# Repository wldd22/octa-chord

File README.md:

# Octa Chord

A 12-key MIDI keyboard with rotary encoders, key switches, and capacitive touch pads.

## Details
PCB made in **KiCad**<br>
Firmware in **KMK**

**Components**:
- **Waveshare ESP32-S3-Zero**: Microcontroller
- **MPR121 Breakout V12**: Capacitive Touch Sensor Control Module
- **Kailh Choc v1 Switches**: Key switches
- **Chocfox CFX Choc Blank Keycaps**: Keycaps
- **Hongyan EC11H 7CE20P1ZD20**: Rotary encoders

**Features**:
- **12 capacitive touch pad keys**, one octave on a piano
- **6 key switches** in a **3x2 grid**, each with an **LED**
- **2 rotary encoders** with switches
- **ESP32 microcontroller** with a **USB-C port** and **15 GPIO pins**

## About
Before making this project, I barely knew anything about MIDI, but I was curious to learn how it
worked and use it to make simple music. So, for week 2 (Music week) of Hack Club's Half Life, I
was excited to make a simple MIDI controller I could use and learn from.

My original plan was far more ambitious than the final version. See [JOURNAL.md](JOURNAL.md) for some
of the many iterations I went through of the layout and overall design. I had to make many compromises
and changes so the final product was useful, feasible, and something I could be happy with.

## Images

### Schematic

### PCB Routing

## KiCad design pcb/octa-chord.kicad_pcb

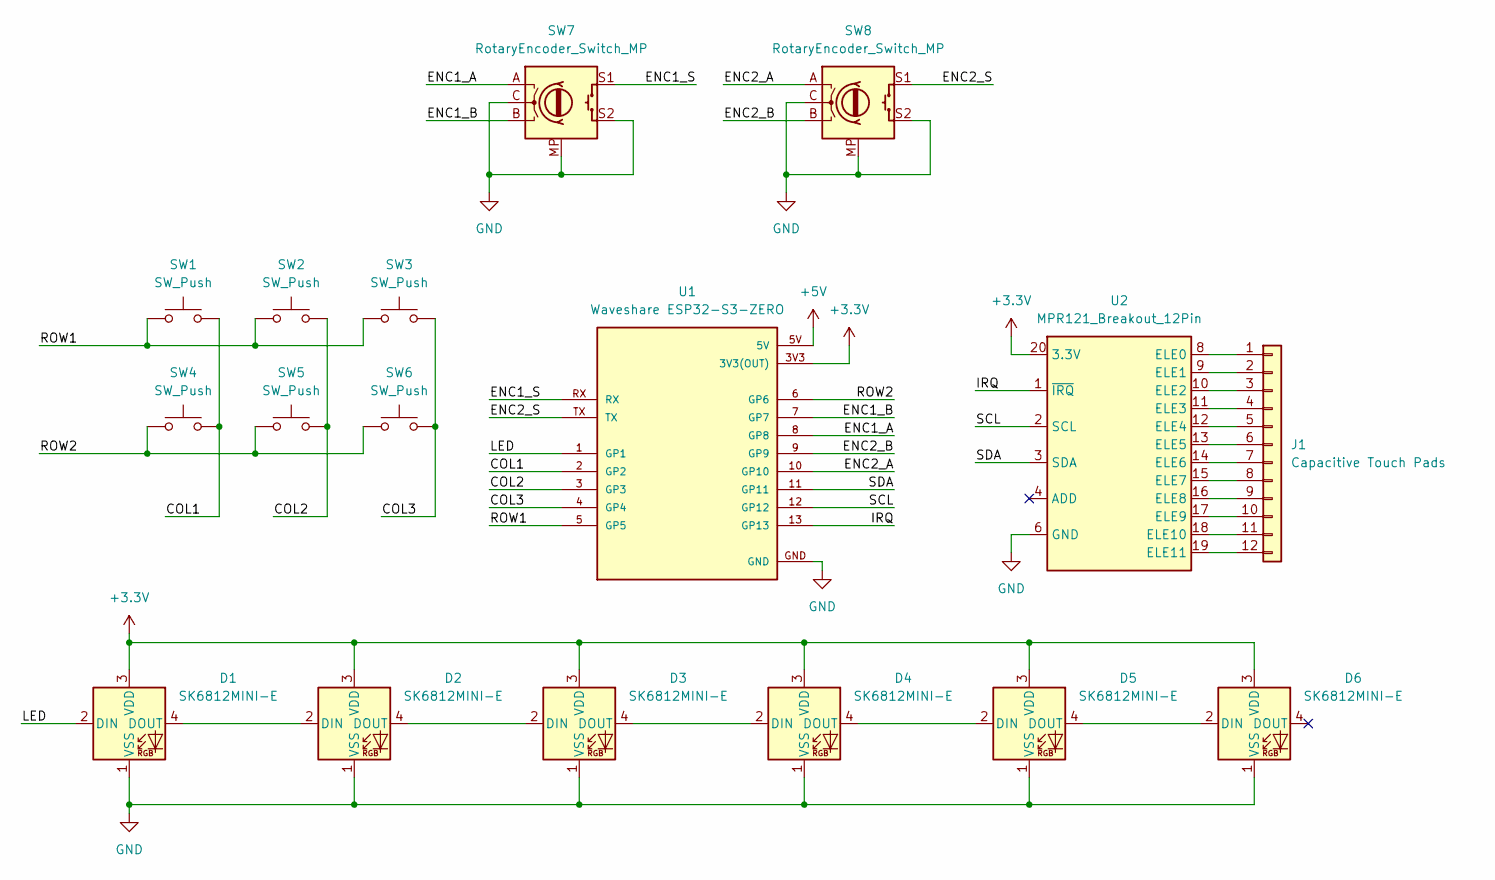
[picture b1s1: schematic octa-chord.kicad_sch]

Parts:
D1, D2, D3, D4, D5, D6: SK6812MINI-E; LED_SK6812MINI-E_3.2x2.8mm_P1.5mm_ReverseMount
J1: Capacitive Touch Pads; Capactive Key Octave
SW1, SW2, SW3, SW4, SW5, SW6: SW_Push; Kailh Choc Low-Profile Switches
SW7, SW8: RotaryEncoder_Switch_MP; RotaryEncoder_Alps_EC11E-Switch_Vertical_H20mm
U1: Waveshare ESP32-S3-ZERO; Waveshare ESP32-S3-Zero; PARTREV NA
U2: MPR121_Breakout_12Pin

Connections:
+3.3V: D1.3 (VDD), D2.3 (VDD), D3.3 (VDD), D4.3 (VDD), D5.3 (VDD), D6.3 (VDD), U1.3V3 (3V3(OUT)), U2.20 (3.3V)
+5V: U1.5V
/COL1: SW1.2, SW4.2, U1.2 (GP2)
/COL2: SW2.2, SW5.2, U1.3 (GP3)
/COL3: SW3.2, SW6.2, U1.4 (GP4)
/ENC1_A: SW7.A, U1.8 (GP8)
/ENC1_B: SW7.B, U1.7 (GP7)
/ENC1_S: SW7.S1, U1.RX
/ENC2_A: SW8.A, U1.10 (GP10)
/ENC2_B: SW8.B, U1.9 (GP9)
/ENC2_S: SW8.S1, U1.TX
/IRQ: U1.13 (GP13), U2.1 (~IRQ)
/LED: D1.2 (DIN), U1.1 (GP1)
/ROW1: SW1.1, SW2.1, SW3.1, U1.5 (GP5)
/ROW2: SW4.1, SW5.1, SW6.1, U1.6 (GP6)
/SCL: U1.12 (GP12), U2.2 (SCL)
/SDA: U1.11 (GP11), U2.3 (SDA)
GND: D1.1 (VSS), D2.1 (VSS), D3.1 (VSS), D4.1 (VSS), D5.1 (VSS), D6.1 (VSS), SW7.C, SW7.MP, SW7.S2, SW8.C, SW8.MP, SW8.S2, U1.GND, U2.6 (GND)
unnamed: D1.4 (DOUT), D2.2 (DIN)
unnamed: D2.4 (DOUT), D3.2 (DIN)
unnamed: D3.4 (DOUT), D4.2 (DIN)
unnamed: D4.4 (DOUT), D5.2 (DIN)
unnamed: D5.4 (DOUT), D6.2 (DIN)
unnamed: J1.1, U2.8 (ELE0)
unnamed: J1.2, U2.9 (ELE1)
unnamed: J1.3, U2.10 (ELE2)
unnamed: J1.4, U2.11 (ELE3)
unnamed: J1.5, U2.12 (ELE4)
unnamed: J1.6, U2.13 (ELE5)
unnamed: J1.7, U2.14 (ELE6)
unnamed: J1.8, U2.15 (ELE7)
unnamed: J1.9, U2.16 (ELE8)
unnamed: J1.10, U2.17 (ELE9)
unnamed: J1.11, U2.18 (ELE10)
unnamed: J1.12, U2.19 (ELE11)

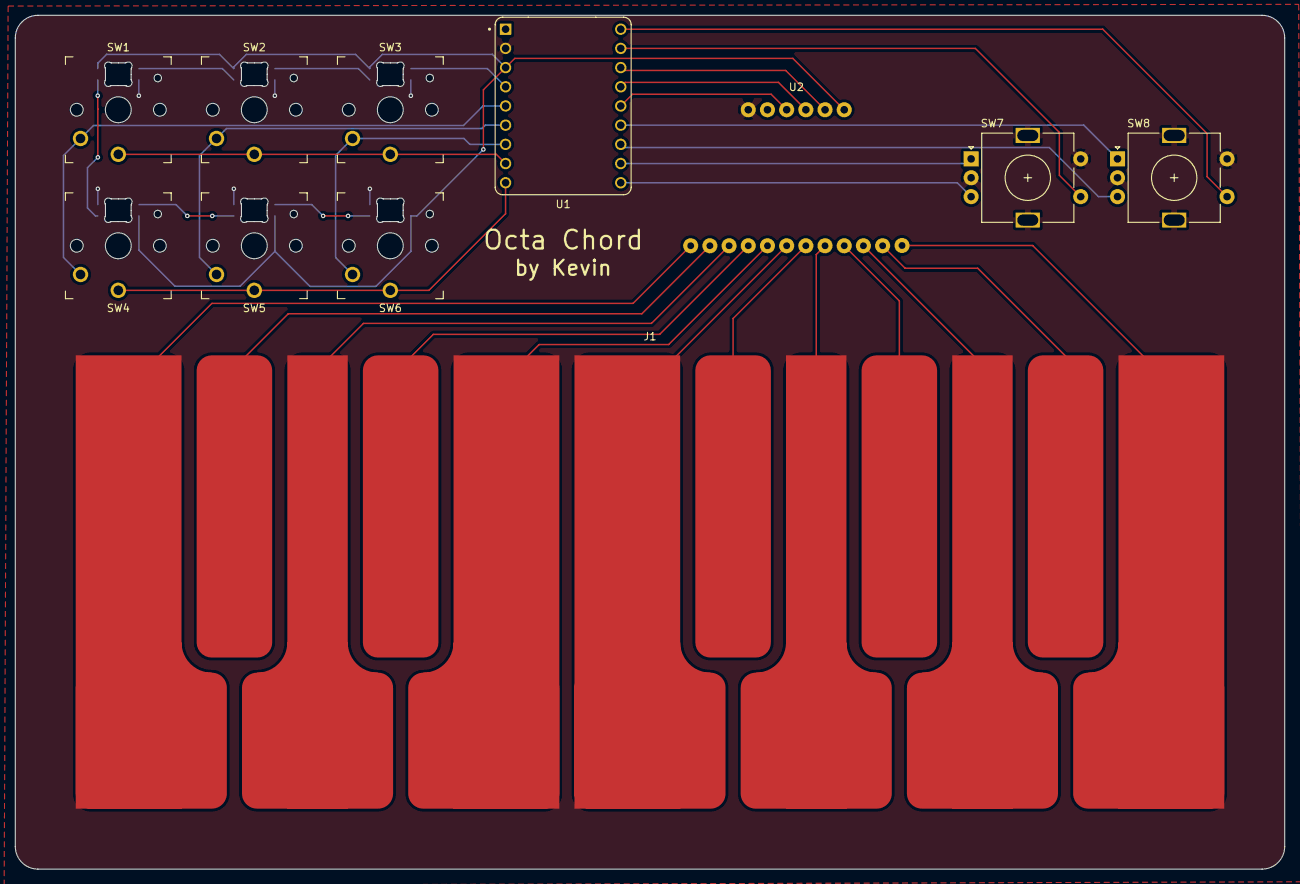
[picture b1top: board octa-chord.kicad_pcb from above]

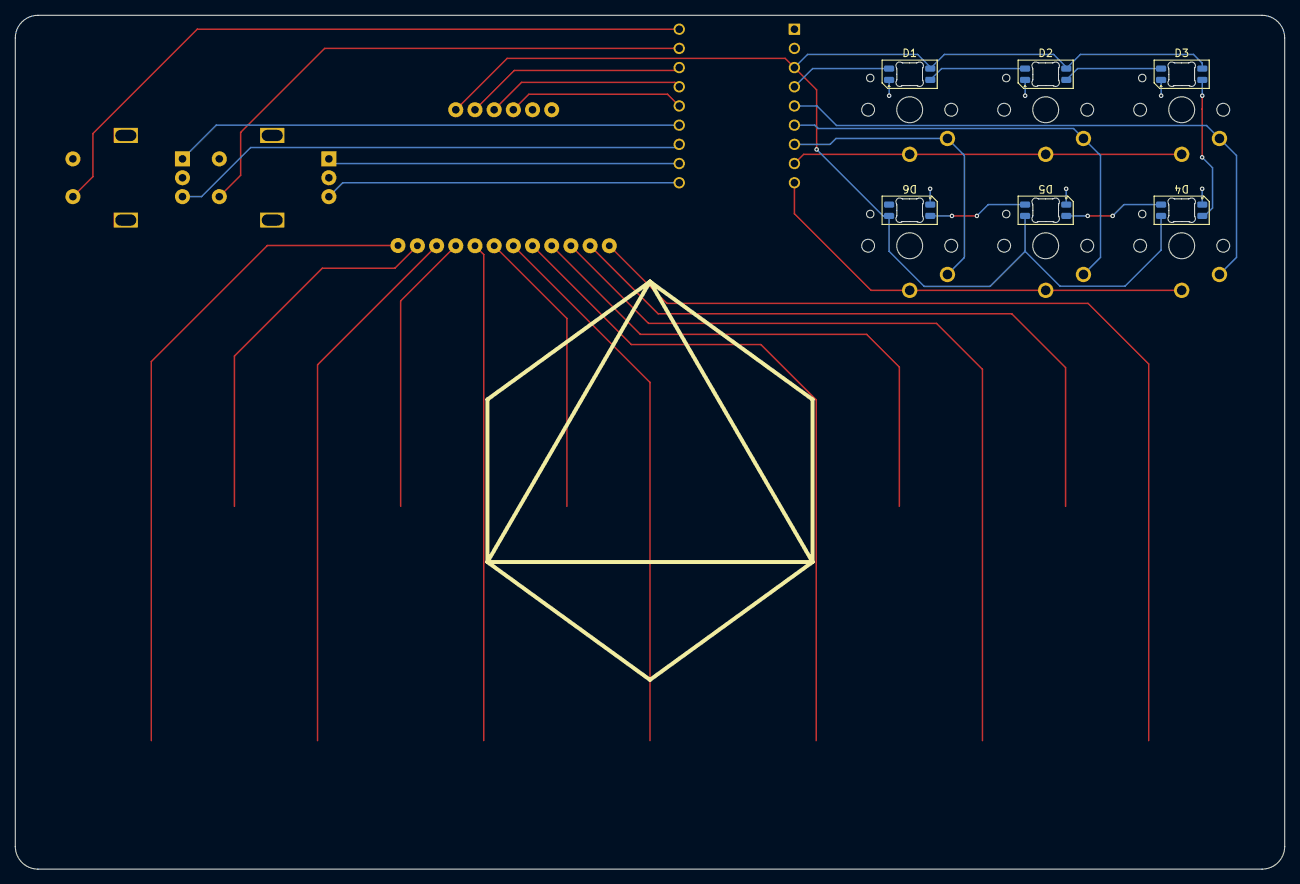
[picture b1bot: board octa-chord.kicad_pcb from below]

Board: 2 copper layers, 168.0 x 113.0 mm, 17 parts (6 on the bottom side), 34 nets.
